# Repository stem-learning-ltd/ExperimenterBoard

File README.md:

Arduino experimenter board
==========================

The concept of this board was developed by C. Paterson to complement an Arduino board for an introduction to "physical computing" at a York CAS Hub meeting at the [National STEM Centre](http://www.nationalstemcentre.org.uk "National STEM Centre website").

The board design and all design files are released under a [Creative Commons Attribution ShareAlike license](http://creativecommons.org/licenses/by-sa/3.0/).

The PCBs were produced by [Hackvana](http://www.hackvana.com "Hackvana website")

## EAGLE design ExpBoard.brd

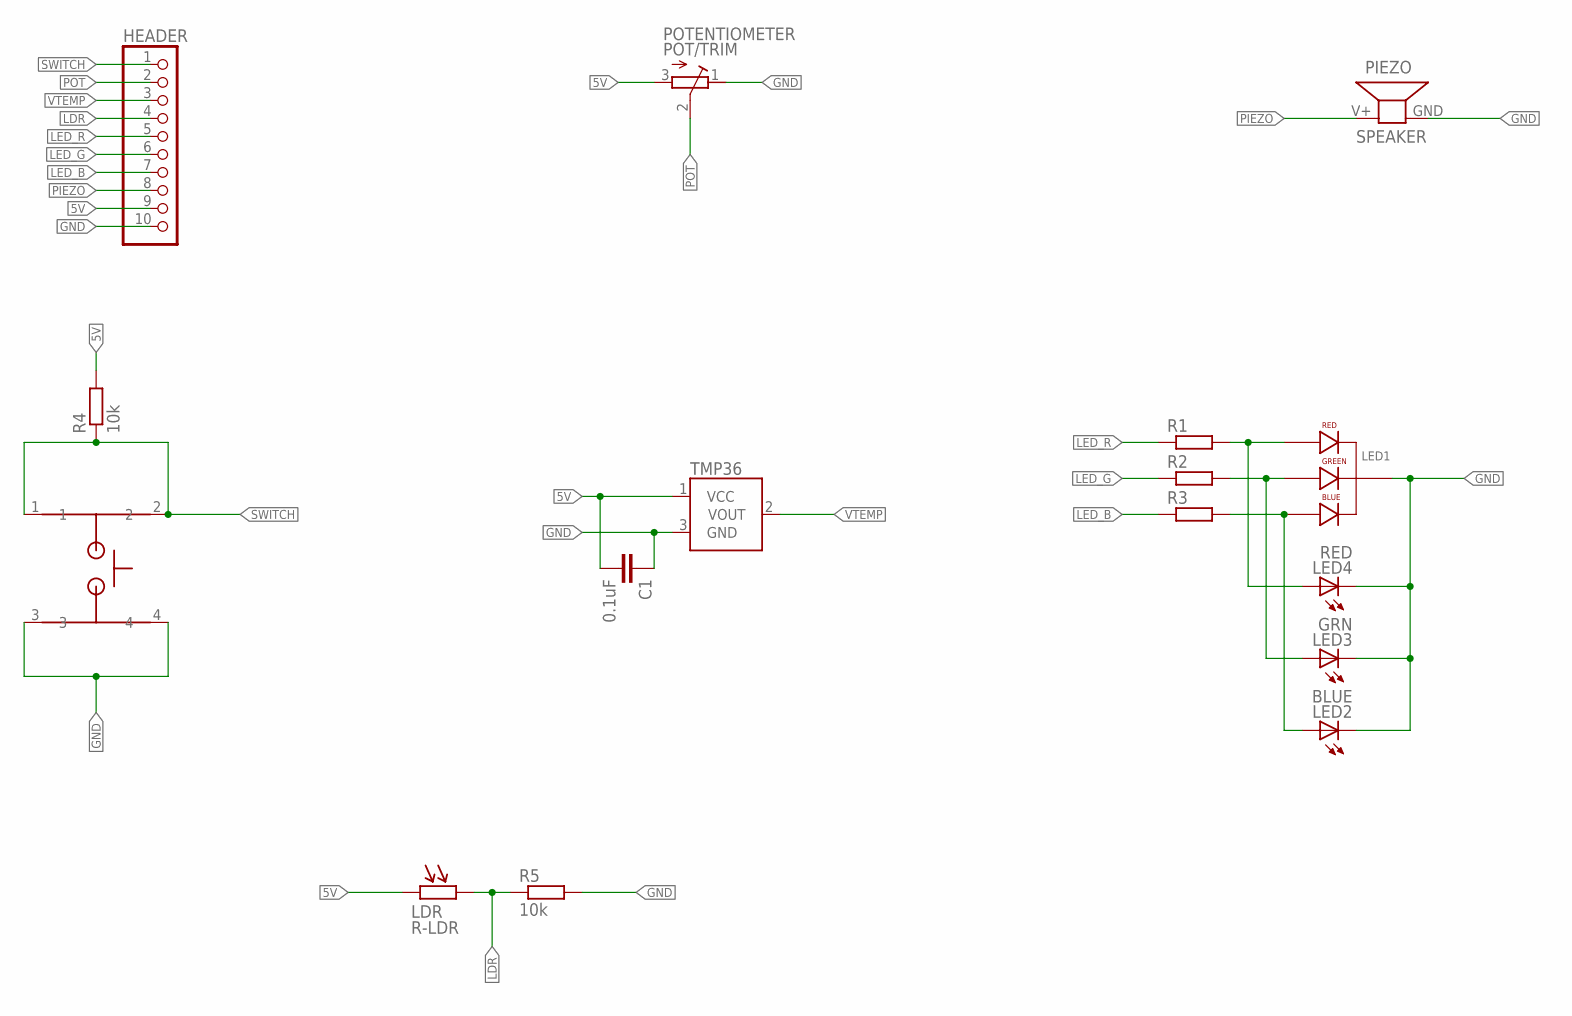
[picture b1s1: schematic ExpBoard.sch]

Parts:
C1: 0.1uF; C050-035X075
HEADER: PINHD-1X10; 1X10
LDR: R-LDR; LDR_RE04698
LED1: LED; LED-RGB-TH
LED2: BLUE; LED5MM
LED3: GRN; LED5MM
LED4: RED; LED5MM
PIEZO: SPEAKER; PIEZO_LS03781
POTENTIOMETER: POT/TRIM; TRIM_RE06540
R1, R2, R3: R-EU_0204/7; 0204/7
R4, R5: 10k; 0204/7
SWITCH: SWITCH; SKHHAMA010
TMP36: TMP36GT9; TO-92

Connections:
5V: C1.2, HEADER.9, LDR.1, POTENTIOMETER.3 (E), R4.2, TMP36.1 (VCC)
GND: C1.1, HEADER.10, LED1.3 (CATHODE), LED2.K (C), LED3.K (C), LED4.K (C), PIEZO.GND (2), POTENTIOMETER.1 (A), R5.2, SWITCH.3, SWITCH.4, TMP36.3 (GND)
LDR: HEADER.4, LDR.2, R5.1
LED_B: HEADER.7, R3.1
LED_G: HEADER.6, R2.1
LED_R: HEADER.5, R1.1
unnamed: LED1.4 (RED_ANODE), LED4.A, R1.2
unnamed: LED1.2 (GREEN_ANODE), LED3.A, R2.2
unnamed: LED1.1 (BLUE_ANODE), LED2.A, R3.2
PIEZO: HEADER.8, PIEZO.V+ (1)
POT: HEADER.2, POTENTIOMETER.2 (S)
SWITCH: HEADER.1, R4.1, SWITCH.1, SWITCH.2
VTEMP: HEADER.3, TMP36.2 (VOUT)

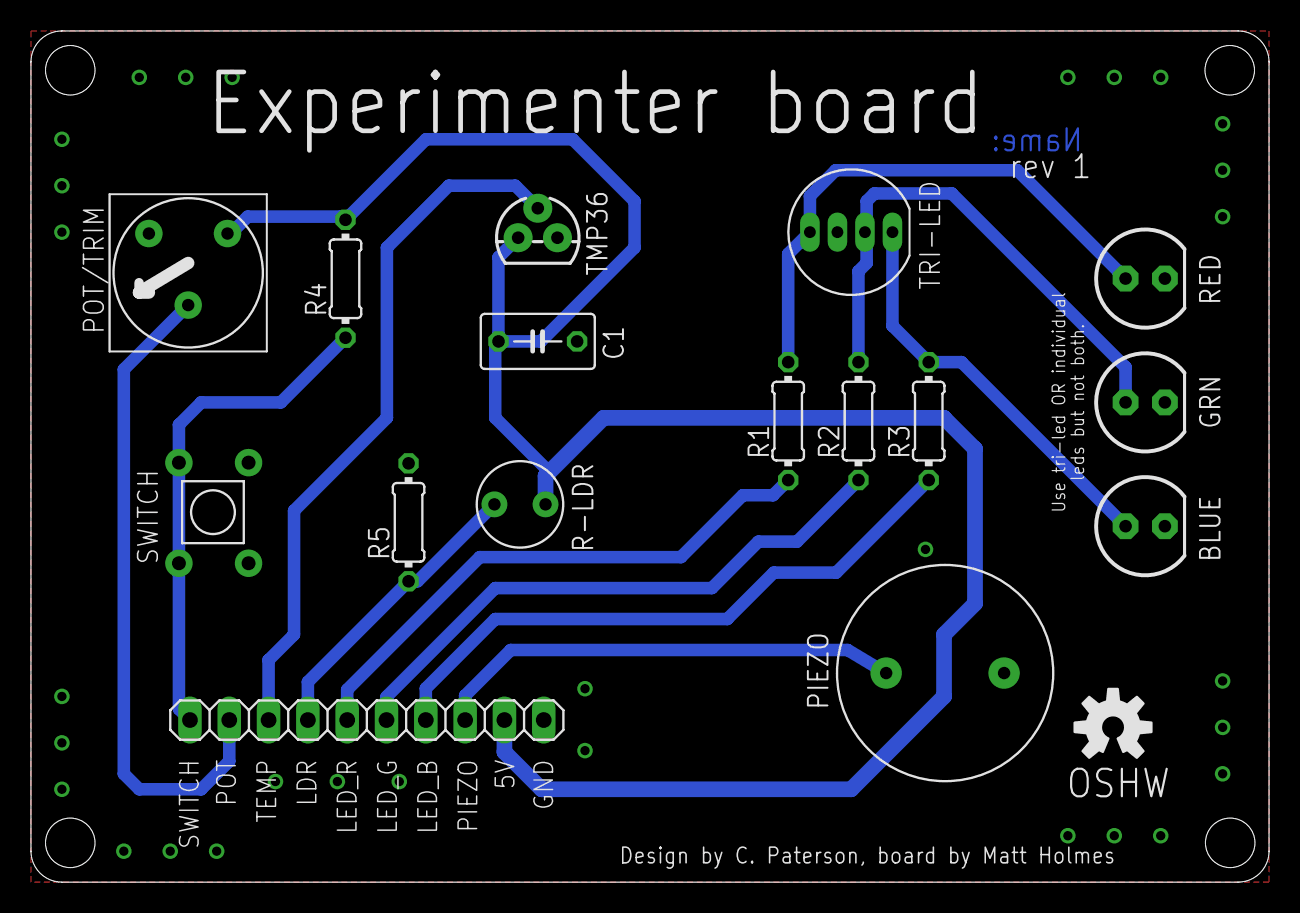
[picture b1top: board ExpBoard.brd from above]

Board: 2 copper layers, 80.0 x 55.0 mm, 18 parts (0 on the bottom side), 13 nets.

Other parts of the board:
U$1: OSHW-LOGO-M
U$2: OSHW-LOGO-L

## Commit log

2013-06-17 Initial commit
    Revision 1 board complete
2013-06-17 Added initial BoM and README
2013-06-17 Tweaked the README
2013-06-17 Added CC license to README
2013-06-17 Tweaked README
2013-07-03 Updates BoM with exact components used
2013-07-05 Added image of completed board

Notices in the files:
ExpBoard.brd:
Creative Commons Attribution ShareAlike 3.0
parts and their libraries:
SparkFun-Sensors: Licensing: CC v3.0 Share-Alike You are welcome to use this library for commercial purposes.
